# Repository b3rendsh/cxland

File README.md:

# cxland
common coleco, msx and retro computer cp/m software and hardware

## Colecovision

[Colecovision games on a Z180 retro computer](https://github.com/b3rendsh/cvload)

## MSX

RomWBW for CP/M (and work-alike) operating systems on a MSX computer:  
[Binaries and instructions](msx/bin)  
[webmsx romwbw test](https://webmsx.org/?MACHINE=MSX2E&RAMMAPPER_SIZE=2048&HARDDISK_URL=https://drive.usercontent.google.com/download?id=1lQBfm3Im3guW6nKrGnGQIzwMFiWn7H08)  
[Sources](https://github.com/b3rendsh/RomWBW)

## Retro computer

[MSX 1 system on a rcbus computer](https://github.com/b3rendsh/msxbase/tree/main/rcbus)  

## Applications

[Tutorial for seting up CP/NET 1.2 via serial](https://github.com/b3rendsh/cxland/blob/main/apps/cpnet/cpnet_tutorial.md)  
[IDE disk info and test program](https://github.com/b3rendsh/cxland/tree/main/apps/taste)  
[TMS video adapter info](https://github.com/b3rendsh/cxland/tree/main/apps/tmsinfo)  

## Hardware

[**RCBUS TN9K - MSX/Coleco compatible video adapter**](https://github.com/b3rendsh/cxland/tree/main/hardware/rcbus-vdp9k)  
 The card uses the Tang Nano 9K FPGA to emulate the TMS9918A (F18A) and V9938/V9958 VDP with 32K VRAM.  
 It can be set to MSX mode or Colecovision mode with a few dip switches and it supports the V9938 80 columns text mode.

**RCBUS AUDIOJOY - MSX/Coleco compatible audio and joystick adapter**  
Design and documentation are under construction.

## License

The Creative Commons license terms applies to all material in this repository with following exceptions.  
MSX-DOS binaries are copyrighted by ASCII and their license terms and/or intentions are respected.  
For the RomWBW binaries and sources the GNU AFFERO GENERAL PUBLIC LICENSE applies.

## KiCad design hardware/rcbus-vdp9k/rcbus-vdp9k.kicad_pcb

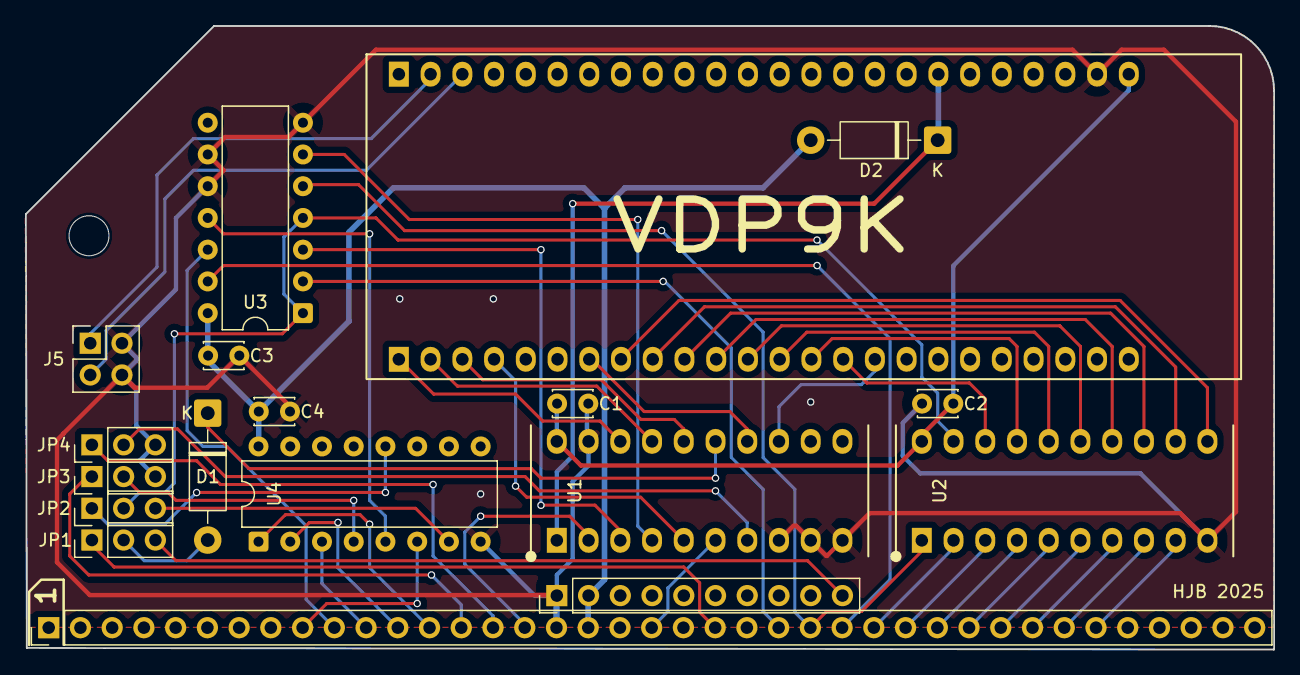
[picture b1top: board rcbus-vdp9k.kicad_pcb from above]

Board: 2 copper layers, 99.9 x 49.9 mm, 19 parts (0 on the bottom side), 52 nets.

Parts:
C1, C2, C3, C4: 0.1uF; C_Disc_D3.0mm_W2.0mm_P2.50mm
D1, D2: 1N5817; D_DO-41_SOD81_P10.16mm_Horizontal
J1: Conn_01X39; PinHeader_1x39_P2.54mm_Vertical
J2: Conn_01x10; PinHeader_1x10_P2.54mm_Vertical
J5: Conn_02x02; PinHeader_2x02_P2.54mm_Vertical
JP1, JP2, JP3, JP4: Jumper_3_Open; PinHeader_1x03_P2.54mm_Vertical
MNT0: MountingHole_3.2mm_M3
U1, U2: SN74LVC245AN; DIP-20_TI-N
U3: 74HCT32; DIP-14_W7.62mm
U4: 74HCT138; DIP-16_W7.62mm
U6: Tang_Nano_9K; DIP-48_TangNano9K

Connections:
+3.3V: C1.1, C2.1, U1.20 (Vcc), U2.20 (Vcc), U6.25 (3V3)
/3VD0: U2.11 (B8), U6.8 (28_IOB11B)
/3VD1: U2.12 (B7), U6.9 (29_IOB13A)
/3VD2: U2.13 (B6), U6.10 (30_IOB13B)
/3VD3: U2.14 (B5), U6.11 (33_IOB23A)
/3VD4: U2.15 (B4), U6.12 (34_IOB23B)
/3VD5: U2.16 (B3), U6.13 (40_IOB33B)
/3VD6: U2.17 (B2), U6.14 (35_IOB29A)
/3VD7: U2.18 (B1), U6.15 (41_IOB41A)
/32Sprites: J5.1, U6.47 (86_IOT8A_1V8)
/COL: JP2.3 (B), U4.7 (O7)
/MODE03: U1.18 (B1), U6.1 (38_IOB31B)
/MODE13: U1.13 (B6), U6.16 (42_IOB41B)
/MSX: JP2.1 (A), U4.12 (O3)
/Scanlines: J5.3, U6.46 (85_IOT8B_1V8)
/VDD: D2.1 (K), U1.1 (DIR), U6.31 (5V)
//CSR: U1.4 (A3), U3.6
//CSR3: U1.16 (B3), U6.3 (36_IOB29B)
//CSW: U1.3 (A2), U3.3
//CSW3: U1.17 (B2), U6.2 (37_IOB31A)
//INT3: U1.5 (A4), U6.4 (39_IOB33A)
//IRQ: D1.1 (K), U1.15 (B4)
//RST3: U1.14 (B5), U6.7 (27_IOB11A)
A0: J1.16, U1.2 (A1)
A1: J1.15, JP4.1 (A)
A2: J1.14, JP3.1 (A)
A3: J1.13, U4.1 (A0)
A4: J1.12, U4.2 (A1)
A5: J1.11, U4.3 (A2)
A6: J1.10, U3.12
A7: J1.9, U4.6 (E3)
D0: J1.27, U2.2 (A1)
D1: J1.28, U2.3 (A2)
D2: J1.29, U2.4 (A3)
D3: J1.30, U2.5 (A4)
D4: J1.31, U2.6 (A5)
D5: J1.32, U2.7 (A6)
D6: J1.33, U2.8 (A7)
D7: J1.34, U2.9 (A8)
GND: C1.2, C2.2, C3.2, C4.2, J1.17, J2.1, J5.2, J5.4, JP3.3 (B), JP4.3 (B), U1.8 (A7), U1.9 (A8), U1.10 (GND), U1.19 (~OE), U2.10 (GND), U3.7 (GND), U3.9, U3.10, U4.8 (GND), U6.26 (GND)
unnamed: D1.2 (A), JP1.2 (C)
unnamed: JP2.2 (C), U2.19 (~OE), U3.1, U3.4
unnamed: JP3.2 (C), U4.4 (E1)
unnamed: JP4.2 (C), U1.7 (A6)
unnamed: U3.11, U4.5 (E2)
VCC: C3.1, C4.1, D2.2 (A), J1.18, J2.2, U3.14 (VCC), U4.16 (VCC)
/INT: J1.22, JP1.1 (A)
/IORQ: J1.26, U3.13
/NMI: J2.10, JP1.3 (B)
/RD: J1.25, U2.1 (DIR), U3.5
/RST: J1.20, U1.6 (A5)
/WR: J1.24, U3.2

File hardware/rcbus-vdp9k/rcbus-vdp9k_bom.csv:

Id,Designator,Footprint,Quantity,Designation
1,"D1,D2","D_DO-41_SOD81_P10.16mm_Horizontal",2,1N5817
2,"U1,U2",DIP-20_TI-N,2,SN74LVC245AN
3,U3,DIP-14_W7.62mm,1,74HCT32
4,U4,DIP-16_W7.62mm,1,74HCT138
5,U6,DIP-48_TangNano9K,1,Tang_Nano_9K
6,"C1,C2,C3,C4",C_Disc_D3.0mm_W2.0mm_P2.50mm,4,0.1uF
7,J1,PinHeader_2x40_P2.54mm_Angled,1,Conn_02X40
8,"JP1,JP2,JP3,JP4",PinHeader_1x03_P2.54mm_Vertical,4,Conn_01x03
9,J5,PinHeader_2x02_P2.54mm_Vertical,1,Conn_02x02

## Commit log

2025-09-17 RomWBW for MSX
    Initial upload trial version
2025-09-17 documentation
2025-09-18 update documentation
2025-10-03 Update RomWBW for MSX
    RomWBW 3.6.0-dev.30 binaries and instructions
2025-10-20 Update binaries
    Update RomWBW for MSX binaries and disk images
2025-10-21 Removed msx351
    Removed old test version of RomWBW 3.51 for MSX
2025-12-15 hardware rcbus vdp9k v2.1
    MSX and Colecovision compatible Tang Nano 9K videocard for rcbus
2025-12-16 RomWBW MSX combo disk image
    Update msx combo disk image with the latest RomWBW build and added draft version of the msx combo build scripts.
2025-12-16 Update RomWBW for MSX disk image
    Added compatibility with old beer 1.9rc driver to boot from the FAT12 partition (marked active)
2026-01-06 update msx combo build script
    Updated readme and added msxrom.com
2026-01-12 removed msx combo disk creation scripts
    msx combo disk creation is now part of the main RomWBW distribution
2026-02-03 RomWBW TMS Device Utility
    Utility to display TMS device information
2026-02-04 update tmsinfo
2026-03-27 Apps: taste and tmsinfo
2026-03-30 RomWBW v3.6.0 for MSX
    update to latest release
2026-04-01 update taste info
2026-04-19 Update readme.md
    Added custom configuration instructions for MALT and SODA interfaces.
2026-05-09 CP/NET tutorial
    Tutorial for setting up CP/NET 1.2 via serial on RomWBW systems
2026-05-09 Update CP/NET tutorial
    Added files and instructions to increase speed on MSX to 115K2 baud
2026-05-11 Update CP/NET tutorial
2026-05-11 Update README.md
    Added links to Apps and Hardware
2026-05-16 cp/net snios for hbios serial
    Optimized SNIOS for use with RomWBW HBIOS serial ports
2026-05-18 update cp/net for hbios serial
    moved sources to separate cpnet-z80 repository fork
